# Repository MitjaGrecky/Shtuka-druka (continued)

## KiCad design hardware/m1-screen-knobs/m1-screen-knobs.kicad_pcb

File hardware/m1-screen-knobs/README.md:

# M1 - screen knobs module

**Current source (R148, 14.11.2026): rev 0.5** - four TI LP5864 (one per pair of rings), 12 RGB LEDs per ring, 4 corner holes + 3 in the gaps (x 56, 112, 168 mm, P97), 163 parts. `gen/design.py` builds rev 0.5 by default; `M1_LP=0` builds the old rev 0.3 (two IS31FL3741A, 13 LEDs, 8 holes), kept for history. The KiCad files here and `hardware/for-routing/M1` agree. The text below still describes rev 0.1-0.3.

Eight smooth encoders with push and touch (Param 1-8 under the screen), each with a ring of 13 RGB LEDs.
Spec and reasoning: `docs/ru/30_m1_screen_knobs.md`. Status: rev 0.1 - schematic done, board routed except 4 connections around U1 (see UNROUTED), light guide ready to print.

| | |
|---|---|
| Board | 224 x 34 mm, 4 layers; panel position x 108.75-332.75, y 263-297 (knob row y 277, panel fold y 300) |
| Top side | 8 x Alps EC11E (smooth, switch), 104 x XINGLIGHT XL-1615RGBC-RF (LCSC C965840) |
| Bottom side | IS31FL3741A LED driver (C2940604), CY8CMBR3108 touch (C462528), 3 x 74HC165, passives, J1 |
| Bus J1 | 2 x 7, 1.27 mm: +5V x2, +3V3, GND x4, SDA, SCL, INT, SR_LOAD, SR_CLK, SR_OUT, SR_IN |
| I2C | LED driver 0x30 (ADDR=GND, R3; 0x31-0x33 via R4-R6), touch 0x37 |
| LED matrix | LED n = 13 (ring-1) + (dot-1): SW = n mod 9 + 1, CS = 3 (n div 9) + 1..3 (R, G, B); CS37-39 unused |
| Shift chain | host reads U3 D7..D0, U4, U5: E1 A, E1 B, E1 push, E2 A, ... E8 push |

## Files

- `m1-screen-knobs.kicad_pro/.kicad_sch/.kicad_pcb` - open in KiCad 10 (written in the KiCad 7 format; KiCad 10 upgrades on save).
- `mech/m1_light_guide.stl` - the light guide (R126), black PETG/PLA, 0.2 mm layers.
- `lib/` - project symbols (IS31FL3741A, XL-1615RGBC-RF, encoder with touch pin) and footprints (LED 1615, QFN-60).
- `gen/` - the generators. Edit `design.py`, then run:

```
python3 gen/make_lib.py     # symbols and footprints
python3 gen/make_sch.py     # schematic
python3 gen/make_pcb.py     # board: placement, nets, GND planes (needs KiCad's pcbnew module)
python3 gen/make_pcb.py --route freerouting-1.9.0.jar --passes 16 --finish   # + autorouting (xvfb-run, Java)
python3 gen/make_pcb.py --ses gen/last_route.ses --finish                     # rebuild from the last routing
python3 gen/make_light_guide.py mech             # light guide STL (needs bpy)
```

`UNROUTED` marks the board as not routed yet: CI keeps the DRC report but does not fail.
`QUILTER.md` - rules for handing the board to an external layout service; the parts fixed by the panel are locked.

License: CERN-OHL-S-2.0 (hardware), AGPL-3.0-or-later (scripts).

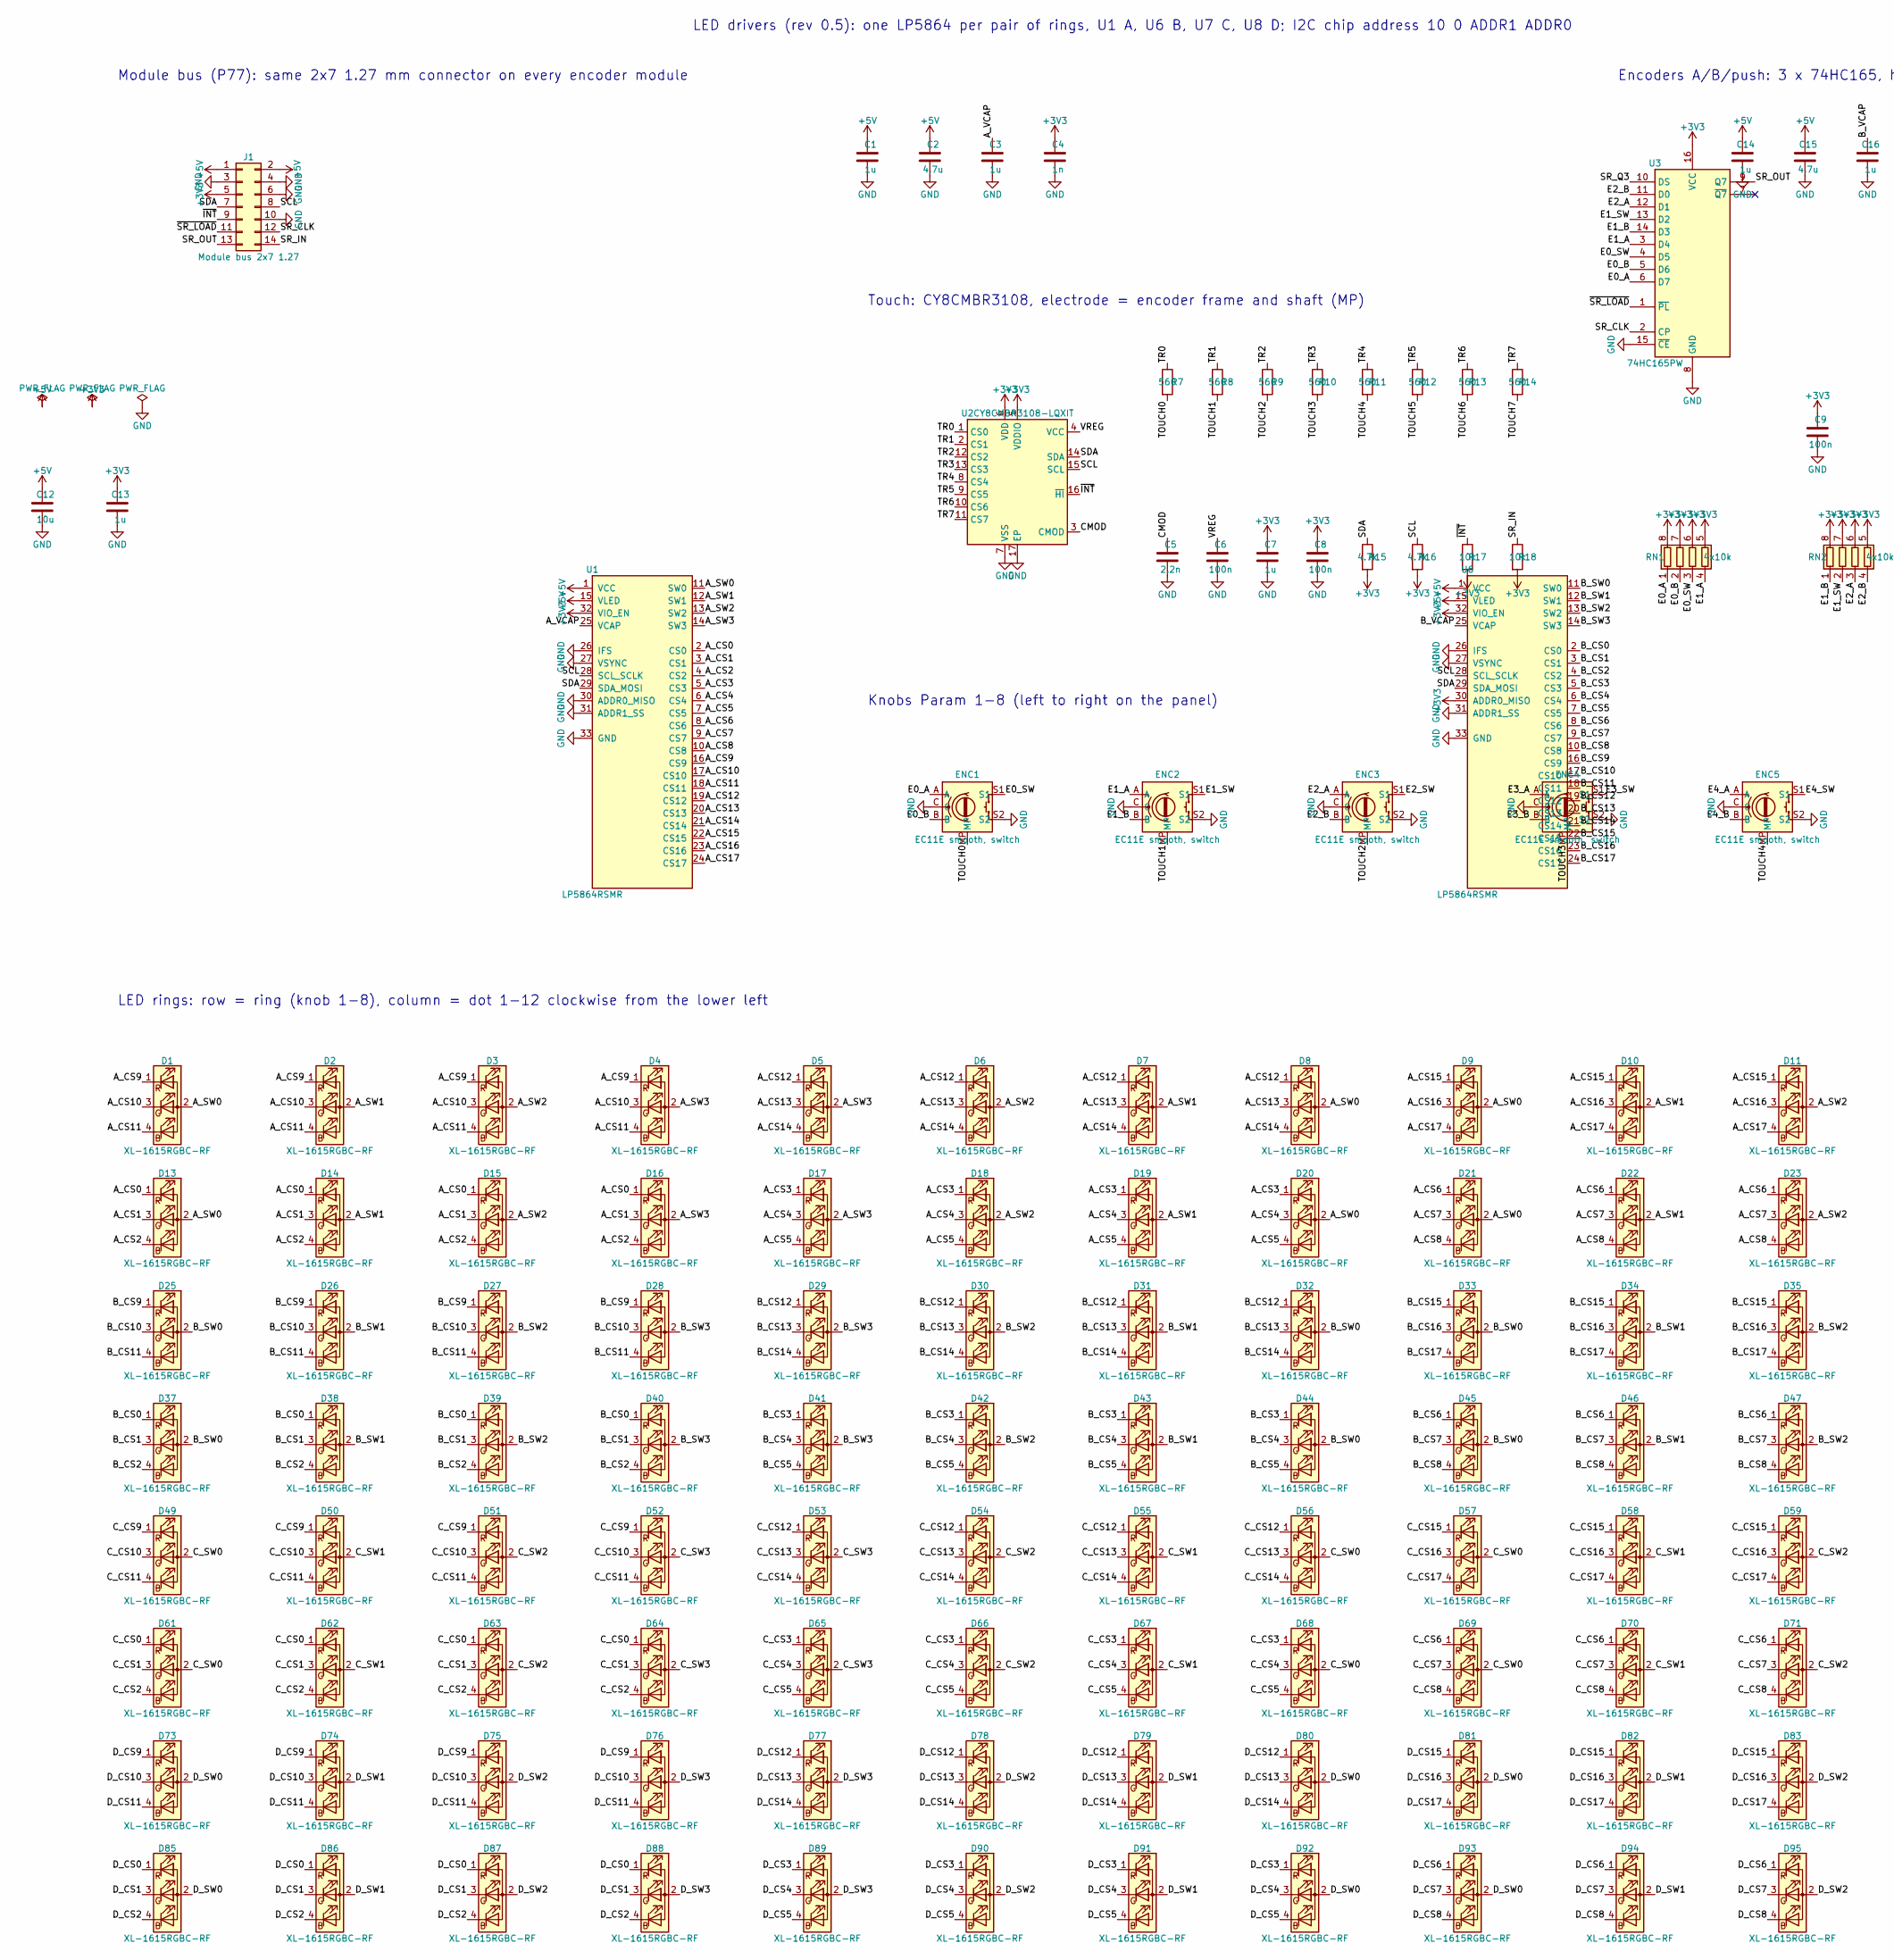
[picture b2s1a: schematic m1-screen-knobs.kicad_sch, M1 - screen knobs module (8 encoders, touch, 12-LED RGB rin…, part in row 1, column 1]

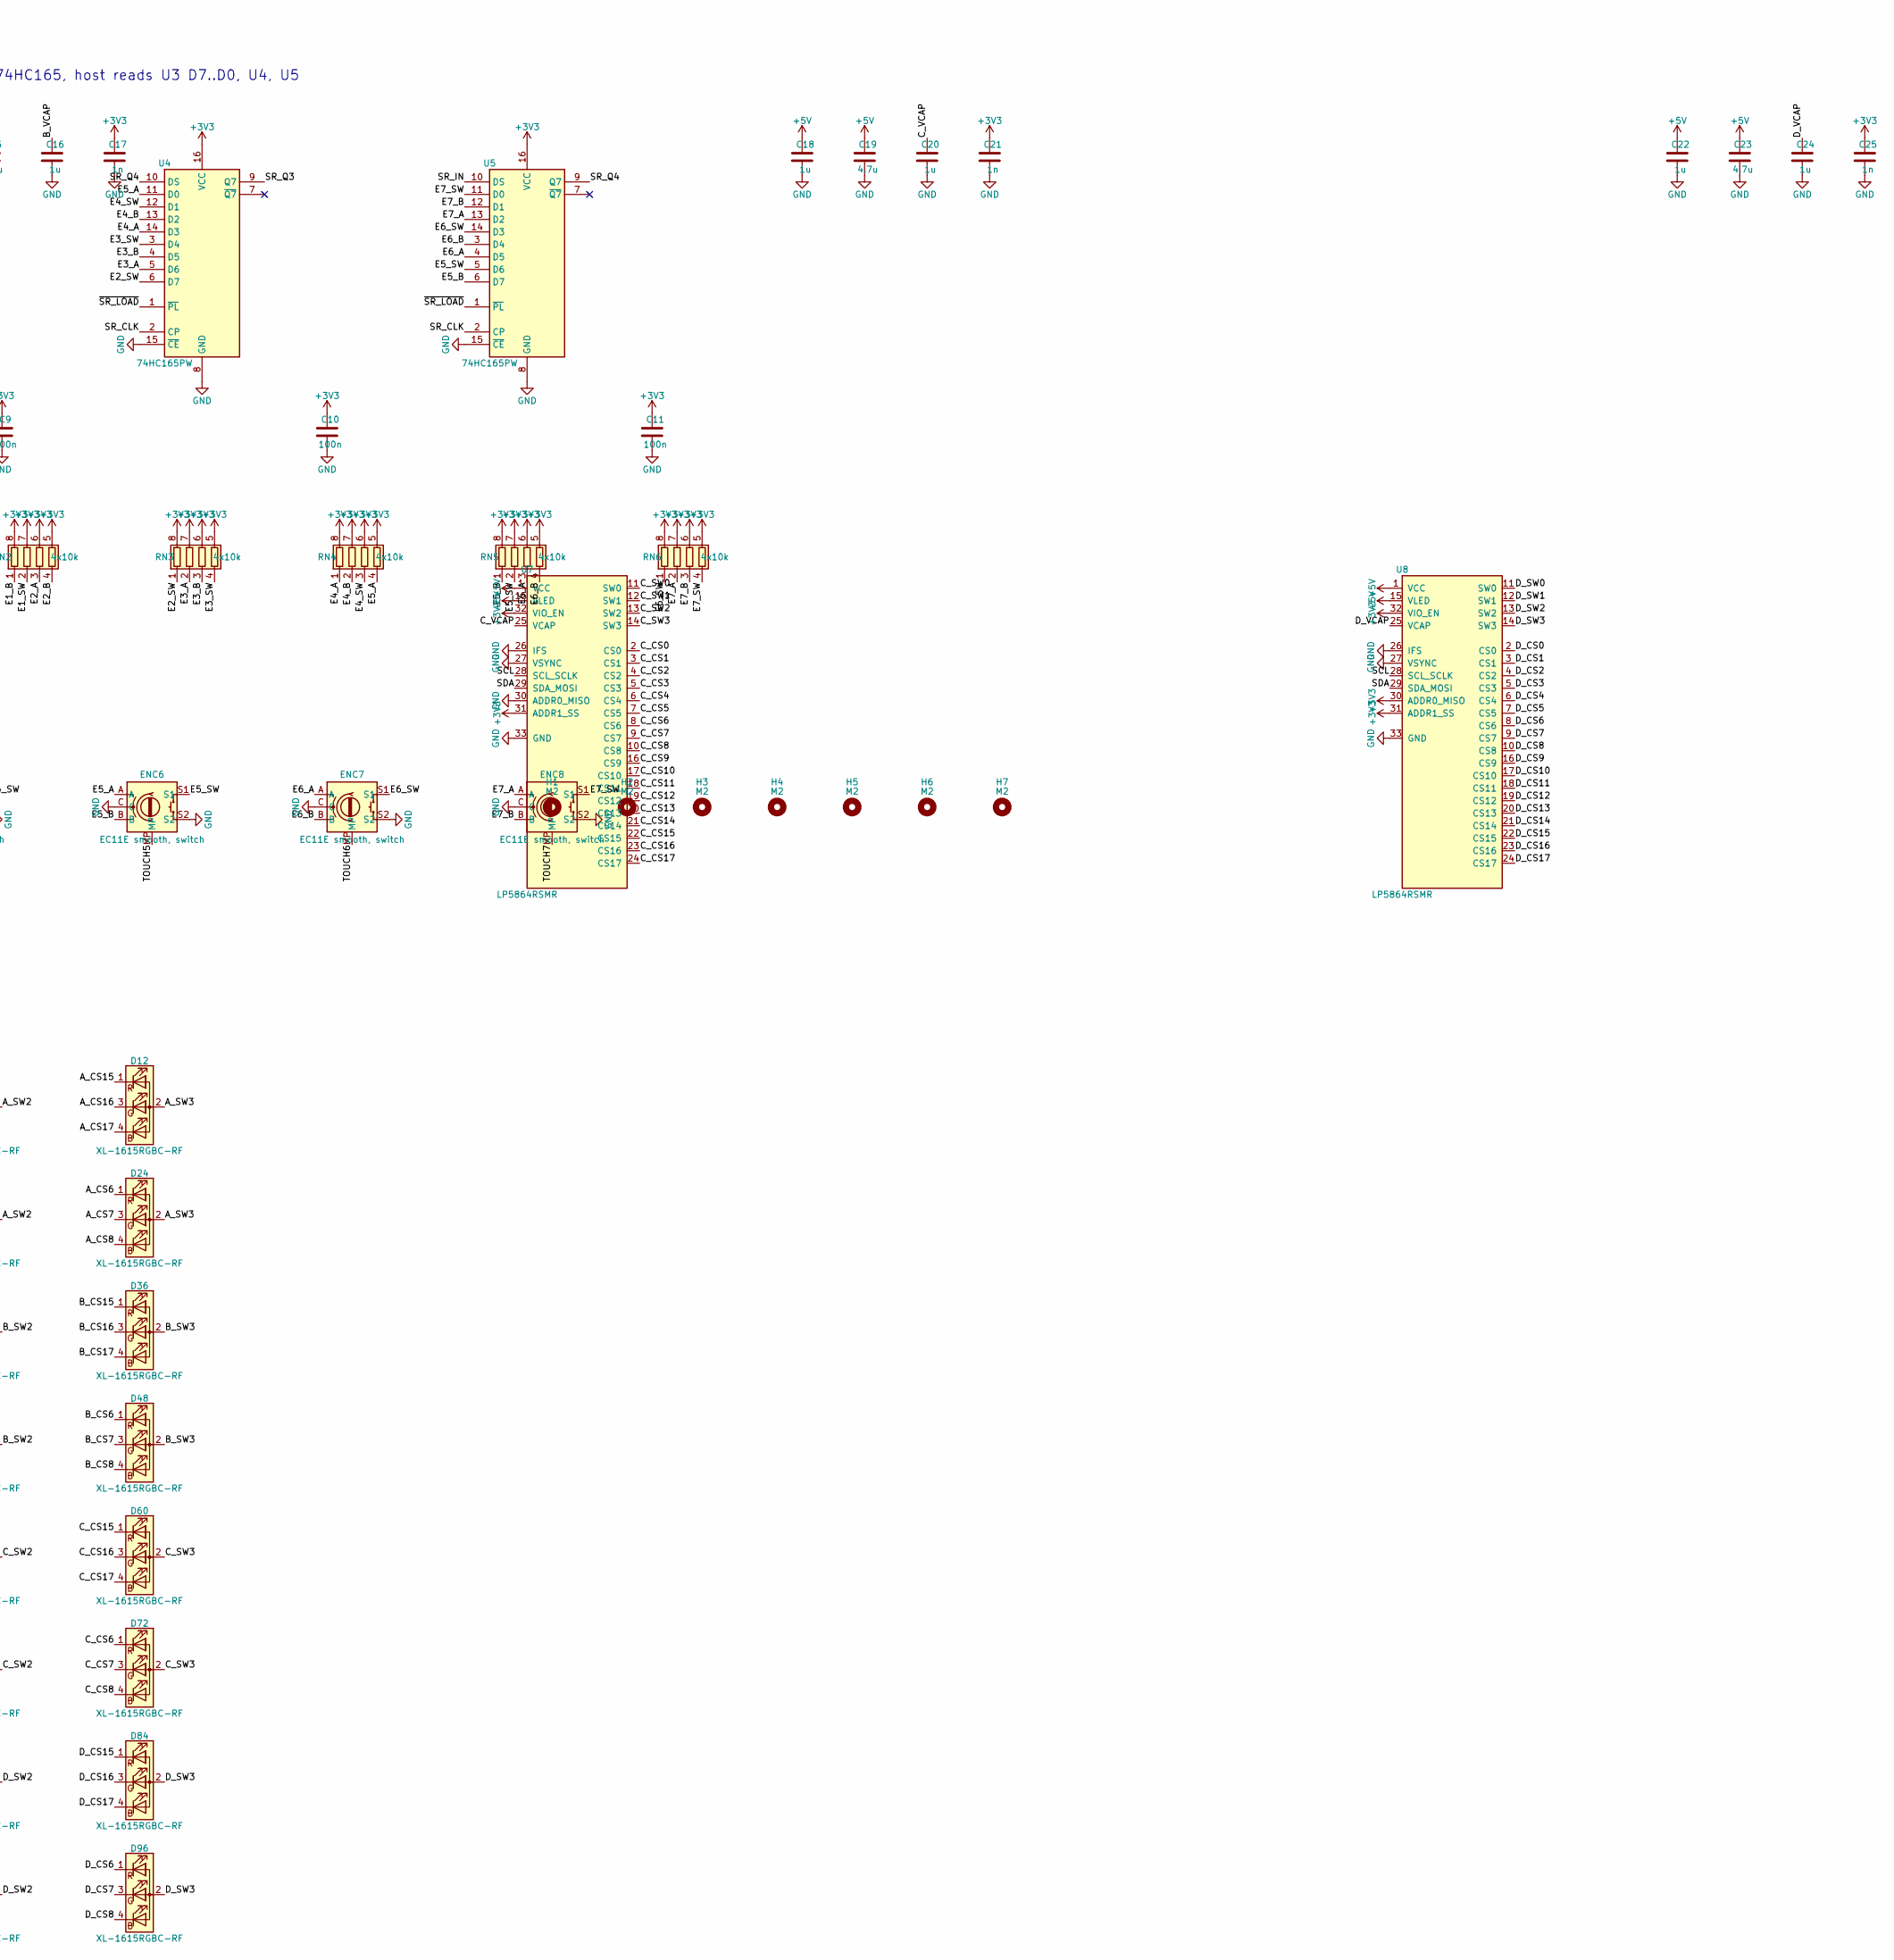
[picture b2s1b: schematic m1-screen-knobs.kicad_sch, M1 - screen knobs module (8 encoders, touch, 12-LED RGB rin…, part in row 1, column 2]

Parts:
C1, C3, C7, C13, C14, C16, C18, C20, C22, C24: 1u; C_0402_1005Metric
C2, C15, C19, C23: 4.7u; C_0805_2012Metric
C4, C17, C21, C25: 1n; C_0402_1005Metric
C5: 2.2n; C_0402_1005Metric
C6, C8, C9, C10, C11: 100n; C_0402_1005Metric
C12: 10u; C_0805_2012Metric
D1, D2, D3, D4, D5, D6, D7, D8, D9, D10, D11, D12, D13, D14, D15, D16, D17, D18, D19, D20, D21, D22, D23, D24, D25, D26, D27, D28, D29, D30, D31, D32, D33, D34, D35, D36, D37, D38, D39, D40, D41, D42, D43, D44, D45, D46, D47, D48, D49, D50, D51, D52, D53, D54, D55, D56, D57, D58, D59, D60, D61, D62, D63, D64, D65, D66, D67, D68, D69, D70, D71, D72, D73, D74, D75, D76, D77, D78, D79, D80, D81, D82, D83, D84, D85, D86, D87, D88, D89, D90, D91, D92, D93, D94, D95, D96: XL-1615RGBC-RF; LED_RGB_XL-1615RGBC_1.6x1.5mm; LCSC C965840
ENC1, ENC2, ENC3, ENC4, ENC5, ENC6, ENC7, ENC8: EC11E smooth, switch; RotaryEncoder_Alps_EC11E-Switch_Vertical_H20mm_Ring
H1, H2, H3, H4, H5, H6, H7: M2; MountingHole_2.2mm_M2
J1: Module bus 2x7 1.27; PinHeader_2x07_P1.27mm_Vertical
R7, R8, R9, R10, R11, R12, R13, R14: 560; R_0402_1005Metric
R15, R16: 4.7k; R_0402_1005Metric
R17, R18: 10k; R_0402_1005Metric
RN1, RN2, RN3, RN4, RN5, RN6: 4x10k; R_Array_Convex_4x0402
U1, U6, U7, U8: LP5864RSMR; VQFN-32-1EP_4x4mm_P0.4mm_EP2.8x2.8mm; LCSC C5220564
U2: CY8CMBR3108-LQXIT; QFN-16-1EP_3x3mm_P0.5mm_EP1.7x1.7mm; LCSC C462528
U3, U4, U5: 74HC165PW; TSSOP-16_4.4x5mm_P0.65mm

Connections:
+3V3: C4.1, C7.1, C8.1, C9.1, C10.1, C11.1, C13.1, C17.1, C21.1, C25.1, J1.5, R15.2, R16.2, R17.2, R18.2, RN1.5 (R4.2), RN1.6 (R3.2), RN1.7 (R2.2), RN1.8 (R1.2), RN2.5 (R4.2), RN2.6 (R3.2), RN2.7 (R2.2), RN2.8 (R1.2), RN3.5 (R4.2), RN3.6 (R3.2), RN3.7 (R2.2), RN3.8 (R1.2), RN4.5 (R4.2), RN4.6 (R3.2), RN4.7 (R2.2), RN4.8 (R1.2), RN5.5 (R4.2), RN5.6 (R3.2), RN5.7 (R2.2), RN5.8 (R1.2), RN6.5 (R4.2), RN6.6 (R3.2), RN6.7 (R2.2), RN6.8 (R1.2), U1.32 (VIO_EN), U2.5 (VDDIO), U2.6 (VDD), U3.16 (VCC), U4.16 (VCC), U5.16 (VCC), U6.30 (ADDR0_MISO), U6.32 (VIO_EN), U7.31 (ADDR1_SS), U7.32 (VIO_EN), U8.30 (ADDR0_MISO), U8.31 (ADDR1_SS), U8.32 (VIO_EN)
+5V: C1.1, C2.1, C12.1, C14.1, C15.1, C18.1, C19.1, C22.1, C23.1, J1.1, J1.2, U1.1 (VCC), U1.15 (VLED), U6.1 (VCC), U6.15 (VLED), U7.1 (VCC), U7.15 (VLED), U8.1 (VCC), U8.15 (VLED)
/A_CS0: D13.1 (RK), D14.1 (RK), D15.1 (RK), D16.1 (RK), U1.2 (CS0)
/A_CS1: D13.3 (GK), D14.3 (GK), D15.3 (GK), D16.3 (GK), U1.3 (CS1)
/A_CS2: D13.4 (BK), D14.4 (BK), D15.4 (BK), D16.4 (BK), U1.4 (CS2)
/A_CS3: D17.1 (RK), D18.1 (RK), D19.1 (RK), D20.1 (RK), U1.5 (CS3)
/A_CS4: D17.3 (GK), D18.3 (GK), D19.3 (GK), D20.3 (GK), U1.6 (CS4)
/A_CS5: D17.4 (BK), D18.4 (BK), D19.4 (BK), D20.4 (BK), U1.7 (CS5)
/A_CS6: D21.1 (RK), D22.1 (RK), D23.1 (RK), D24.1 (RK), U1.8 (CS6)
/A_CS7: D21.3 (GK), D22.3 (GK), D23.3 (GK), D24.3 (GK), U1.9 (CS7)
/A_CS8: D21.4 (BK), D22.4 (BK), D23.4 (BK), D24.4 (BK), U1.10 (CS8)
/A_CS9: D1.1 (RK), D2.1 (RK), D3.1 (RK), D4.1 (RK), U1.16 (CS9)
/A_CS10: D1.3 (GK), D2.3 (GK), D3.3 (GK), D4.3 (GK), U1.17 (CS10)
/A_CS11: D1.4 (BK), D2.4 (BK), D3.4 (BK), D4.4 (BK), U1.18 (CS11)
/A_CS12: D5.1 (RK), D6.1 (RK), D7.1 (RK), D8.1 (RK), U1.19 (CS12)
/A_CS13: D5.3 (GK), D6.3 (GK), D7.3 (GK), D8.3 (GK), U1.20 (CS13)
/A_CS14: D5.4 (BK), D6.4 (BK), D7.4 (BK), D8.4 (BK), U1.21 (CS14)
/A_CS15: D9.1 (RK), D10.1 (RK), D11.1 (RK), D12.1 (RK), U1.22 (CS15)
/A_CS16: D9.3 (GK), D10.3 (GK), D11.3 (GK), D12.3 (GK), U1.23 (CS16)
/A_CS17: D9.4 (BK), D10.4 (BK), D11.4 (BK), D12.4 (BK), U1.24 (CS17)
/A_SW0: D1.2 (A), D8.2 (A), D9.2 (A), D13.2 (A), D20.2 (A), D21.2 (A), U1.11 (SW0)
/A_SW1: D2.2 (A), D7.2 (A), D10.2 (A), D14.2 (A), D19.2 (A), D22.2 (A), U1.12 (SW1)
/A_SW2: D3.2 (A), D6.2 (A), D11.2 (A), D15.2 (A), D18.2 (A), D23.2 (A), U1.13 (SW2)
/A_SW3: D4.2 (A), D5.2 (A), D12.2 (A), D16.2 (A), D17.2 (A), D24.2 (A), U1.14 (SW3)
/A_VCAP: C3.1, U1.25 (VCAP)
/B_CS0: D37.1 (RK), D38.1 (RK), D39.1 (RK), D40.1 (RK), U6.2 (CS0)
/B_CS1: D37.3 (GK), D38.3 (GK), D39.3 (GK), D40.3 (GK), U6.3 (CS1)
/B_CS2: D37.4 (BK), D38.4 (BK), D39.4 (BK), D40.4 (BK), U6.4 (CS2)
/B_CS3: D41.1 (RK), D42.1 (RK), D43.1 (RK), D44.1 (RK), U6.5 (CS3)
/B_CS4: D41.3 (GK), D42.3 (GK), D43.3 (GK), D44.3 (GK), U6.6 (CS4)
/B_CS5: D41.4 (BK), D42.4 (BK), D43.4 (BK), D44.4 (BK), U6.7 (CS5)
/B_CS6: D45.1 (RK), D46.1 (RK), D47.1 (RK), D48.1 (RK), U6.8 (CS6)
/B_CS7: D45.3 (GK), D46.3 (GK), D47.3 (GK), D48.3 (GK), U6.9 (CS7)
/B_CS8: D45.4 (BK), D46.4 (BK), D47.4 (BK), D48.4 (BK), U6.10 (CS8)
/B_CS9: D25.1 (RK), D26.1 (RK), D27.1 (RK), D28.1 (RK), U6.16 (CS9)
/B_CS10: D25.3 (GK), D26.3 (GK), D27.3 (GK), D28.3 (GK), U6.17 (CS10)
/B_CS11: D25.4 (BK), D26.4 (BK), D27.4 (BK), D28.4 (BK), U6.18 (CS11)
/B_CS12: D29.1 (RK), D30.1 (RK), D31.1 (RK), D32.1 (RK), U6.19 (CS12)
/B_CS13: D29.3 (GK), D30.3 (GK), D31.3 (GK), D32.3 (GK), U6.20 (CS13)
/B_CS14: D29.4 (BK), D30.4 (BK), D31.4 (BK), D32.4 (BK), U6.21 (CS14)
/B_CS15: D33.1 (RK), D34.1 (RK), D35.1 (RK), D36.1 (RK), U6.22 (CS15)
/B_CS16: D33.3 (GK), D34.3 (GK), D35.3 (GK), D36.3 (GK), U6.23 (CS16)
/B_CS17: D33.4 (BK), D34.4 (BK), D35.4 (BK), D36.4 (BK), U6.24 (CS17)
/B_SW0: D25.2 (A), D32.2 (A), D33.2 (A), D37.2 (A), D44.2 (A), D45.2 (A), U6.11 (SW0)
/B_SW1: D26.2 (A), D31.2 (A), D34.2 (A), D38.2 (A), D43.2 (A), D46.2 (A), U6.12 (SW1)
/B_SW2: D27.2 (A), D30.2 (A), D35.2 (A), D39.2 (A), D42.2 (A), D47.2 (A), U6.13 (SW2)
/B_SW3: D28.2 (A), D29.2 (A), D36.2 (A), D40.2 (A), D41.2 (A), D48.2 (A), U6.14 (SW3)
/B_VCAP: C16.1, U6.25 (VCAP)
/CMOD: C5.1, U2.3 (CMOD)
/C_CS0: D61.1 (RK), D62.1 (RK), D63.1 (RK), D64.1 (RK), U7.2 (CS0)
/C_CS1: D61.3 (GK), D62.3 (GK), D63.3 (GK), D64.3 (GK), U7.3 (CS1)
/C_CS2: D61.4 (BK), D62.4 (BK), D63.4 (BK), D64.4 (BK), U7.4 (CS2)
/C_CS3: D65.1 (RK), D66.1 (RK), D67.1 (RK), D68.1 (RK), U7.5 (CS3)
/C_CS4: D65.3 (GK), D66.3 (GK), D67.3 (GK), D68.3 (GK), U7.6 (CS4)
/C_CS5: D65.4 (BK), D66.4 (BK), D67.4 (BK), D68.4 (BK), U7.7 (CS5)
/C_CS6: D69.1 (RK), D70.1 (RK), D71.1 (RK), D72.1 (RK), U7.8 (CS6)
/C_CS7: D69.3 (GK), D70.3 (GK), D71.3 (GK), D72.3 (GK), U7.9 (CS7)
/C_CS8: D69.4 (BK), D70.4 (BK), D71.4 (BK), D72.4 (BK), U7.10 (CS8)
/C_CS9: D49.1 (RK), D50.1 (RK), D51.1 (RK), D52.1 (RK), U7.16 (CS9)
/C_CS10: D49.3 (GK), D50.3 (GK), D51.3 (GK), D52.3 (GK), U7.17 (CS10)
/C_CS11: D49.4 (BK), D50.4 (BK), D51.4 (BK), D52.4 (BK), U7.18 (CS11)
/C_CS12: D53.1 (RK), D54.1 (RK), D55.1 (RK), D56.1 (RK), U7.19 (CS12)
/C_CS13: D53.3 (GK), D54.3 (GK), D55.3 (GK), D56.3 (GK), U7.20 (CS13)
/C_CS14: D53.4 (BK), D54.4 (BK), D55.4 (BK), D56.4 (BK), U7.21 (CS14)
/C_CS15: D57.1 (RK), D58.1 (RK), D59.1 (RK), D60.1 (RK), U7.22 (CS15)
/C_CS16: D57.3 (GK), D58.3 (GK), D59.3 (GK), D60.3 (GK), U7.23 (CS16)
/C_CS17: D57.4 (BK), D58.4 (BK), D59.4 (BK), D60.4 (BK), U7.24 (CS17)
/C_SW0: D49.2 (A), D56.2 (A), D57.2 (A), D61.2 (A), D68.2 (A), D69.2 (A), U7.11 (SW0)
/C_SW1: D50.2 (A), D55.2 (A), D58.2 (A), D62.2 (A), D67.2 (A), D70.2 (A), U7.12 (SW1)
/C_SW2: D51.2 (A), D54.2 (A), D59.2 (A), D63.2 (A), D66.2 (A), D71.2 (A), U7.13 (SW2)
/C_SW3: D52.2 (A), D53.2 (A), D60.2 (A), D64.2 (A), D65.2 (A), D72.2 (A), U7.14 (SW3)
/C_VCAP: C20.1, U7.25 (VCAP)
/D_CS0: D85.1 (RK), D86.1 (RK), D87.1 (RK), D88.1 (RK), U8.2 (CS0)
/D_CS1: D85.3 (GK), D86.3 (GK), D87.3 (GK), D88.3 (GK), U8.3 (CS1)
/D_CS2: D85.4 (BK), D86.4 (BK), D87.4 (BK), D88.4 (BK), U8.4 (CS2)
/D_CS3: D89.1 (RK), D90.1 (RK), D91.1 (RK), D92.1 (RK), U8.5 (CS3)
/D_CS4: D89.3 (GK), D90.3 (GK), D91.3 (GK), D92.3 (GK), U8.6 (CS4)
/D_CS5: D89.4 (BK), D90.4 (BK), D91.4 (BK), D92.4 (BK), U8.7 (CS5)
/D_CS6: D93.1 (RK), D94.1 (RK), D95.1 (RK), D96.1 (RK), U8.8 (CS6)
/D_CS7: D93.3 (GK), D94.3 (GK), D95.3 (GK), D96.3 (GK), U8.9 (CS7)
/D_CS8: D93.4 (BK), D94.4 (BK), D95.4 (BK), D96.4 (BK), U8.10 (CS8)
/D_CS9: D73.1 (RK), D74.1 (RK), D75.1 (RK), D76.1 (RK), U8.16 (CS9)
/D_CS10: D73.3 (GK), D74.3 (GK), D75.3 (GK), D76.3 (GK), U8.17 (CS10)
/D_CS11: D73.4 (BK), D74.4 (BK), D75.4 (BK), D76.4 (BK), U8.18 (CS11)
/D_CS12: D77.1 (RK), D78.1 (RK), D79.1 (RK), D80.1 (RK), U8.19 (CS12)
/D_CS13: D77.3 (GK), D78.3 (GK), D79.3 (GK), D80.3 (GK), U8.20 (CS13)
/D_CS14: D77.4 (BK), D78.4 (BK), D79.4 (BK), D80.4 (BK), U8.21 (CS14)
/D_CS15: D81.1 (RK), D82.1 (RK), D83.1 (RK), D84.1 (RK), U8.22 (CS15)
/D_CS16: D81.3 (GK), D82.3 (GK), D83.3 (GK), D84.3 (GK), U8.23 (CS16)
/D_CS17: D81.4 (BK), D82.4 (BK), D83.4 (BK), D84.4 (BK), U8.24 (CS17)
/D_SW0: D73.2 (A), D80.2 (A), D81.2 (A), D85.2 (A), D92.2 (A), D93.2 (A), U8.11 (SW0)
/D_SW1: D74.2 (A), D79.2 (A), D82.2 (A), D86.2 (A), D91.2 (A), D94.2 (A), U8.12 (SW1)
/D_SW2: D75.2 (A), D78.2 (A), D83.2 (A), D87.2 (A), D90.2 (A), D95.2 (A), U8.13 (SW2)
/D_SW3: D76.2 (A), D77.2 (A), D84.2 (A), D88.2 (A), D89.2 (A), D96.2 (A), U8.14 (SW3)
/D_VCAP: C24.1, U8.25 (VCAP)
/E0_A: ENC1.A, RN1.1 (R1.1), U3.6 (D7)
/E0_B: ENC1.B, RN1.2 (R2.1), U3.5 (D6)
/E0_SW: ENC1.S1, RN1.3 (R3.1), U3.4 (D5)
/E1_A: ENC2.A, RN1.4 (R4.1), U3.3 (D4)
/E1_B: ENC2.B, RN2.1 (R1.1), U3.14 (D3)
/E1_SW: ENC2.S1, RN2.2 (R2.1), U3.13 (D2)
/E2_A: ENC3.A, RN2.3 (R3.1), U3.12 (D1)
/E2_B: ENC3.B, RN2.4 (R4.1), U3.11 (D0)
/E2_SW: ENC3.S1, RN3.1 (R1.1), U4.6 (D7)
/E3_A: ENC4.A, RN3.2 (R2.1), U4.5 (D6)
/E3_B: ENC4.B, RN3.3 (R3.1), U4.4 (D5)
/E3_SW: ENC4.S1, RN3.4 (R4.1), U4.3 (D4)
/E4_A: ENC5.A, RN4.1 (R1.1), U4.14 (D3)
/E4_B: ENC5.B, RN4.2 (R2.1), U4.13 (D2)
/E4_SW: ENC5.S1, RN4.3 (R3.1), U4.12 (D1)
/E5_A: ENC6.A, RN4.4 (R4.1), U4.11 (D0)
/E5_B: ENC6.B, RN5.1 (R1.1), U5.6 (D7)
/E5_SW: ENC6.S1, RN5.2 (R2.1), U5.5 (D6)
/E6_A: ENC7.A, RN5.3 (R3.1), U5.4 (D5)
/E6_B: ENC7.B, RN5.4 (R4.1), U5.3 (D4)
/E6_SW: ENC7.S1, RN6.1 (R1.1), U5.14 (D3)
/E7_A: ENC8.A, RN6.2 (R2.1), U5.13 (D2)
/E7_B: ENC8.B, RN6.3 (R3.1), U5.12 (D1)
/E7_SW: ENC8.S1, RN6.4 (R4.1), U5.11 (D0)
/SCL: J1.8, R16.1, U1.28 (SCL_SCLK), U2.15 (SCL), U6.28 (SCL_SCLK), U7.28 (SCL_SCLK), U8.28 (SCL_SCLK)
/SDA: J1.7, R15.1, U1.29 (SDA_MOSI), U2.14 (SDA), U6.29 (SDA_MOSI), U7.29 (SDA_MOSI), U8.29 (SDA_MOSI)
/SR_CLK: J1.12, U3.2 (CP), U4.2 (CP), U5.2 (CP)
/SR_IN: J1.14, R18.1, U5.10 (DS)
/SR_OUT: J1.13, U3.9 (Q7)
/SR_Q3: U3.10 (DS), U4.9 (Q7)
/SR_Q4: U4.10 (DS), U5.9 (Q7)
/TOUCH0: ENC1.MP, R7.2
/TOUCH1: ENC2.MP, R8.2
/TOUCH2: ENC3.MP, R9.2
/TOUCH3: ENC4.MP, R10.2
/TOUCH4: ENC5.MP, R11.2
/TOUCH5: ENC6.MP, R12.2
/TOUCH6: ENC7.MP, R13.2
/TOUCH7: ENC8.MP, R14.2
/TR0: R7.1, U2.1 (CS0)
/TR1: R8.1, U2.2 (CS1)
/TR2: R9.1, U2.12 (CS2)
/TR3: R10.1, U2.13 (CS3)
/TR4: R11.1, U2.8 (CS4)
/TR5: R12.1, U2.9 (CS5)
/TR6: R13.1, U2.10 (CS6)
/TR7: R14.1, U2.11 (CS7)
/VREG: C6.1, U2.4 (VCC)
/~INT: J1.9, R17.1, U2.16 (~HI)
/~SR_LOAD: J1.11, U3.1 (~PL), U4.1 (~PL), U5.1 (~PL)
GND: C1.2, C2.2, C3.2, C4.2, C5.2, C6.2, C7.2, C8.2, C9.2, C10.2, C11.2, C12.2, C13.2, C14.2, C15.2, C16.2, C17.2, C18.2, C19.2, C20.2, C21.2, C22.2, C23.2, C24.2, C25.2, ENC1.C, ENC1.S2, ENC2.C, ENC2.S2, ENC3.C, ENC3.S2, ENC4.C, ENC4.S2, ENC5.C, ENC5.S2, ENC6.C, ENC6.S2, ENC7.C, ENC7.S2, ENC8.C, ENC8.S2, J1.3, J1.4, J1.6, J1.10, U1.26 (IFS), U1.27 (VSYNC), U1.30 (ADDR0_MISO), U1.31 (ADDR1_SS), U1.33 (GND), U2.7 (VSS), U2.17 (EP), U3.8 (GND), U3.15 (~CE), U4.8 (GND), U4.15 (~CE), U5.8 (GND), U5.15 (~CE), U6.26 (IFS), U6.27 (VSYNC), U6.31 (ADDR1_SS), U6.33 (GND), U7.26 (IFS), U7.27 (VSYNC), U7.30 (ADDR0_MISO), U7.33 (GND), U8.26 (IFS), U8.27 (VSYNC), U8.33 (GND)

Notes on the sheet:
Module bus (P77): same 2x7 1.27 mm connector on every encoder module
LED drivers (rev 0.5): one LP5864 per pair of rings, U1 A, U6 B, U7 C, U8 D; I2C chip address 10 0 ADDR1 ADDR0
Touch: CY8CMBR3108, electrode = encoder frame and shaft (MP)
Encoders A/B/push: 3 x 74HC165, host reads U3 D7..D0, U4, U5
Knobs Param 1-8 (left to right on the panel)
LED rings: row = ring (knob 1-8), column = dot 1-12 clockwise from the lower left

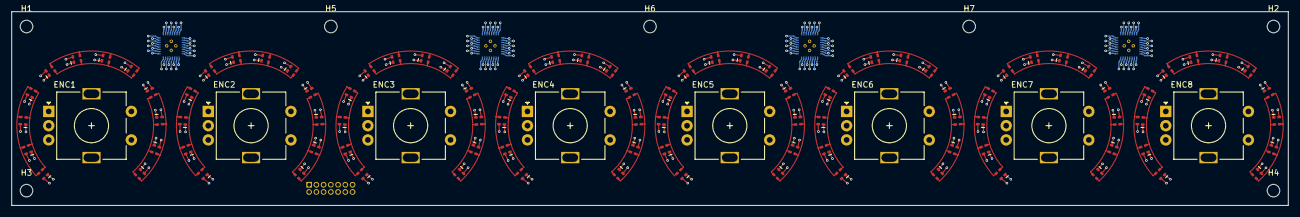
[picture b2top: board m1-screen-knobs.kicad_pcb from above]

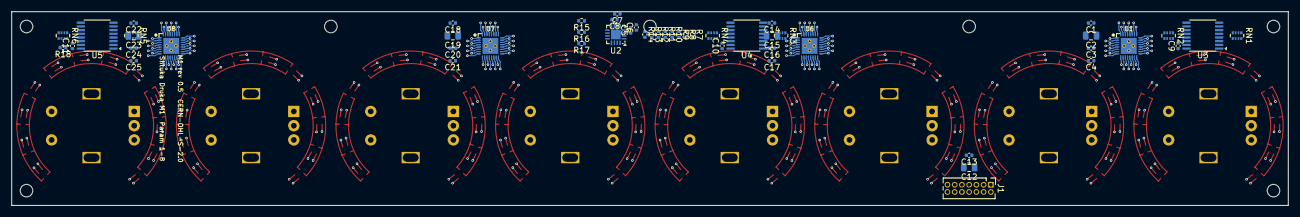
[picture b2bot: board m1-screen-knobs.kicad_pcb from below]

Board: 4 copper layers, 224.0 x 34.0 mm, 163 parts (52 on the bottom side), 146 nets.

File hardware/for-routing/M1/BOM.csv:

Comment,Designator,Footprint,LCSC Part #
Module bus 2x7 1.27,J1,PinHeader_2x07_P1.27mm_Vertical,C5372811
LP5864RSMR,"U1,U6,U7,U8",VQFN-32-1EP_4x4mm_P0.4mm_EP2.8x2.8mm,C5220564
1u,"C1,C3,C7,C13,C14,C16,C18,C20,C22,C24",C_0402_1005Metric,C52923
4.7u,"C2,C15,C19,C23",C_0805_2012Metric,
1n,"C4,C17,C21,C25",C_0402_1005Metric,
CY8CMBR3108-LQXIT,U2,QFN-16-1EP_3x3mm_P0.5mm_EP1.7x1.7mm,C462528
560,"R7,R8,R9,R10,R11,R12,R13,R14",R_0402_1005Metric,
2.2n,C5,C_0402_1005Metric,
100n,"C6,C8,C9,C10,C11",C_0402_1005Metric,C1525
10k,R18,R_0402_1005Metric,C25744
74HC165PW,"U3,U4,U5",TSSOP-16_4.4x5mm_P0.65mm,C80696
4x10k,"RN1,RN2,RN3,RN4,RN5,RN6",R_Array_Convex_4x0402,C25725
10u,C12,C_0805_2012Metric,C15850
"EC11E smooth, switch","ENC1,ENC2,ENC3,ENC4,ENC5,ENC6,ENC7,ENC8",RotaryEncoder_Alps_EC11E-Switch_Vertical_H20mm_Ring,
XL-1615RGBC-RF,"D1,D2,D3,D4,D5,D6,D7,D8,D9,D10,D11,D12,D13,D14,D15,D16,D17,D18,D19,D20,D21,D22,D23,D24,D25,D26,D27,D28,D29,D30,D31,D32,D33,D34,D35,D36,D37,D38,D39,D40,D41,D42,D43,D44,D45,D46,D47,D48,D49,D50,D51,D52,D53,D54,D55,D56,D57,D58,D59,D60,D61,D62,D63,D64,D65,D66,D67,D68,D69,D70,D71,D72,D73,D74,D75,D76,D77,D78,D79,D80,D81,D82,D83,D84,D85,D86,D87,D88,D89,D90,D91,D92,D93,D94,D95,D96",LED_RGB_XL-1615RGBC_1.6x1.5mm,C965840

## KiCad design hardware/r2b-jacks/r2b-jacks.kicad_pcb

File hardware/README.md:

# Hardware

KiCad 10 projects. Each board is generated by Python scripts in its `gen/` folder; CI (`.github/workflows/kicad.yml`)
runs ERC, DRC with schematic parity and exports BOM, Gerbers and placement files on every push.
Board map and reasoning: `docs/ru/29_board_map.md`.

| Board | What | Status | Spec |
|---|---|---|---|
| [`m1-screen-knobs`](m1-screen-knobs/) | 8 encoders with touch and 13-LED rings under the screen | rev 0.1, routing (see `UNROUTED`, `QUILTER.md`) | `docs/ru/30_m1_screen_knobs.md` |
| [`w1-levels`](w1-levels/) | Volume pots, P48 buttons, window for M5 | rev 0.1, routed | `docs/ru/31_w1_levels.md` |

License: CERN Open Hardware Licence Version 2 - Strongly Reciprocal (CERN-OHL-S-2.0), see `LICENSE`.

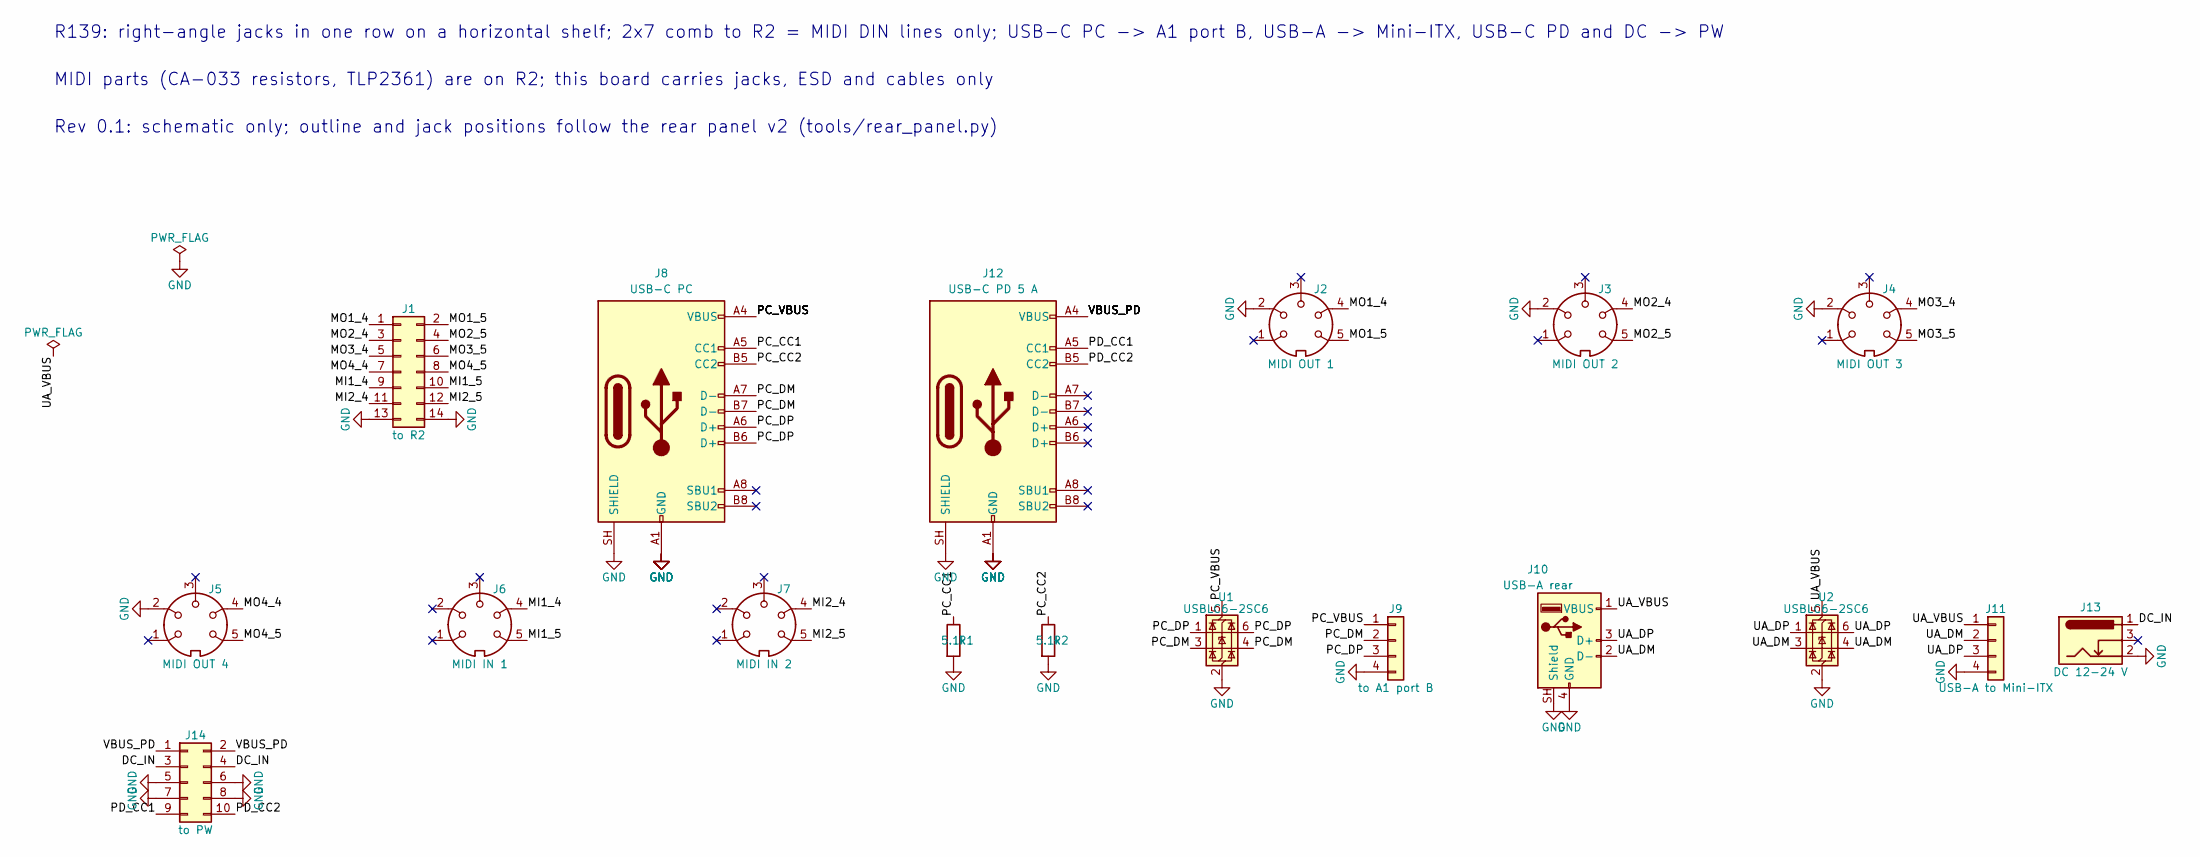
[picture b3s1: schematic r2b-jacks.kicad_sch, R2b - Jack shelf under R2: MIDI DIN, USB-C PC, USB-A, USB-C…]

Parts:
J1: to R2; PinHeader_2x07_P2.54mm_Vertical
J2: MIDI OUT 1; DIN-5_CUI_SDS-50J_Horizontal; LCSC C6216157
J3: MIDI OUT 2; DIN-5_CUI_SDS-50J_Horizontal; LCSC C6216157
J4: MIDI OUT 3; DIN-5_CUI_SDS-50J_Horizontal; LCSC C6216157
J5: MIDI OUT 4; DIN-5_CUI_SDS-50J_Horizontal; LCSC C6216157
J6: MIDI IN 1; DIN-5_CUI_SDS-50J_Horizontal; LCSC C6216157
J7: MIDI IN 2; DIN-5_CUI_SDS-50J_Horizontal; LCSC C6216157
J8: USB-C PC; USB_C_Receptacle_HRO_TYPE-C-31-M-12; LCSC C165948
J9: to A1 port B; JST_PH_B4B-PH-K_1x04_P2.00mm_Vertical
J10: USB-A rear; USB_A_Molex_67643_Horizontal
J11: USB-A to Mini-ITX; JST_PH_B4B-PH-K_1x04_P2.00mm_Vertical
J12: USB-C PD 5 A; USB_C_Receptacle_GCT_USB4105-xx-A_16P_TopMnt_Horizontal; LCSC C3025063
J13: DC 12-24 V; BarrelJack_Kycon_KLDHCX-0202-BC-1_Horizontal; LCSC C19842566
J14: to PW; PinHeader_2x05_P2.54mm_Vertical
R1, R2: 5.1k; R_0402_1005Metric
U1, U2: USBLC6-2SC6; SOT-23-6; LCSC C323793

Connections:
/DC_IN: J13.1, J14.3, J14.4
/MI1_4: J1.9, J6.4
/MI1_5: J1.10, J6.5
/MI2_4: J1.11, J7.4
/MI2_5: J1.12, J7.5
/MO1_4: J1.1, J2.4
/MO1_5: J1.2, J2.5
/MO2_4: J1.3, J3.4
/MO2_5: J1.4, J3.5
/MO3_4: J1.5, J4.4
/MO3_5: J1.6, J4.5
/MO4_4: J1.7, J5.4
/MO4_5: J1.8, J5.5
/PC_CC1: J8.A5 (CC1), R1.1
/PC_CC2: J8.B5 (CC2), R2.1
/PC_DM: J8.A7 (D-), J8.B7 (D-), J9.2, U1.3 (I/O2), U1.4 (I/O2)
/PC_DP: J8.A6 (D+), J8.B6 (D+), J9.3, U1.1 (I/O1), U1.6 (I/O1)
/PC_VBUS: J8.A4 (VBUS), J8.A9 (VBUS), J8.B4 (VBUS), J8.B9 (VBUS), J9.1, U1.5 (VBUS)
/PD_CC1: J12.A5 (CC1), J14.9
/PD_CC2: J12.B5 (CC2), J14.10
/UA_DM: J10.2 (D-), J11.2, U2.3 (I/O2), U2.4 (I/O2)
/UA_DP: J10.3 (D+), J11.3, U2.1 (I/O1), U2.6 (I/O1)
/UA_VBUS: J10.1 (VBUS), J11.1, U2.5 (VBUS)
/VBUS_PD: J12.A4 (VBUS), J12.A9 (VBUS), J12.B4 (VBUS), J12.B9 (VBUS), J14.1, J14.2
GND: J1.13, J1.14, J2.2, J3.2, J4.2, J5.2, J8.A1 (GND), J8.A12 (GND), J8.B1 (GND), J8.B12 (GND), J8.SH (SHIELD), J9.4, J10.4 (GND), J10.SH (Shield), J11.4, J12.A1 (GND), J12.A12 (GND), J12.B1 (GND), J12.B12 (GND), J12.SH (SHIELD), J13.2, J14.5, J14.6, J14.7, J14.8, R1.2, R2.2, U1.2 (GND), U2.2 (GND)

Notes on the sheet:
R139: right-angle jacks in one row on a horizontal shelf; 2x7 comb to R2 = MIDI DIN lines only; USB-C PC -> A1 port B, USB-A -> Mini-ITX, USB-C PD and DC -> PW
MIDI parts (CA-033 resistors, TLP2361) are on R2; this board carries jacks, ESD and cables only
Rev 0.1: schematic only; outline and jack positions follow the rear panel v2 (tools/rear_panel.py)

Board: 2 copper layers, 18 parts (0 on the bottom side), 25 nets, no tracks yet.
